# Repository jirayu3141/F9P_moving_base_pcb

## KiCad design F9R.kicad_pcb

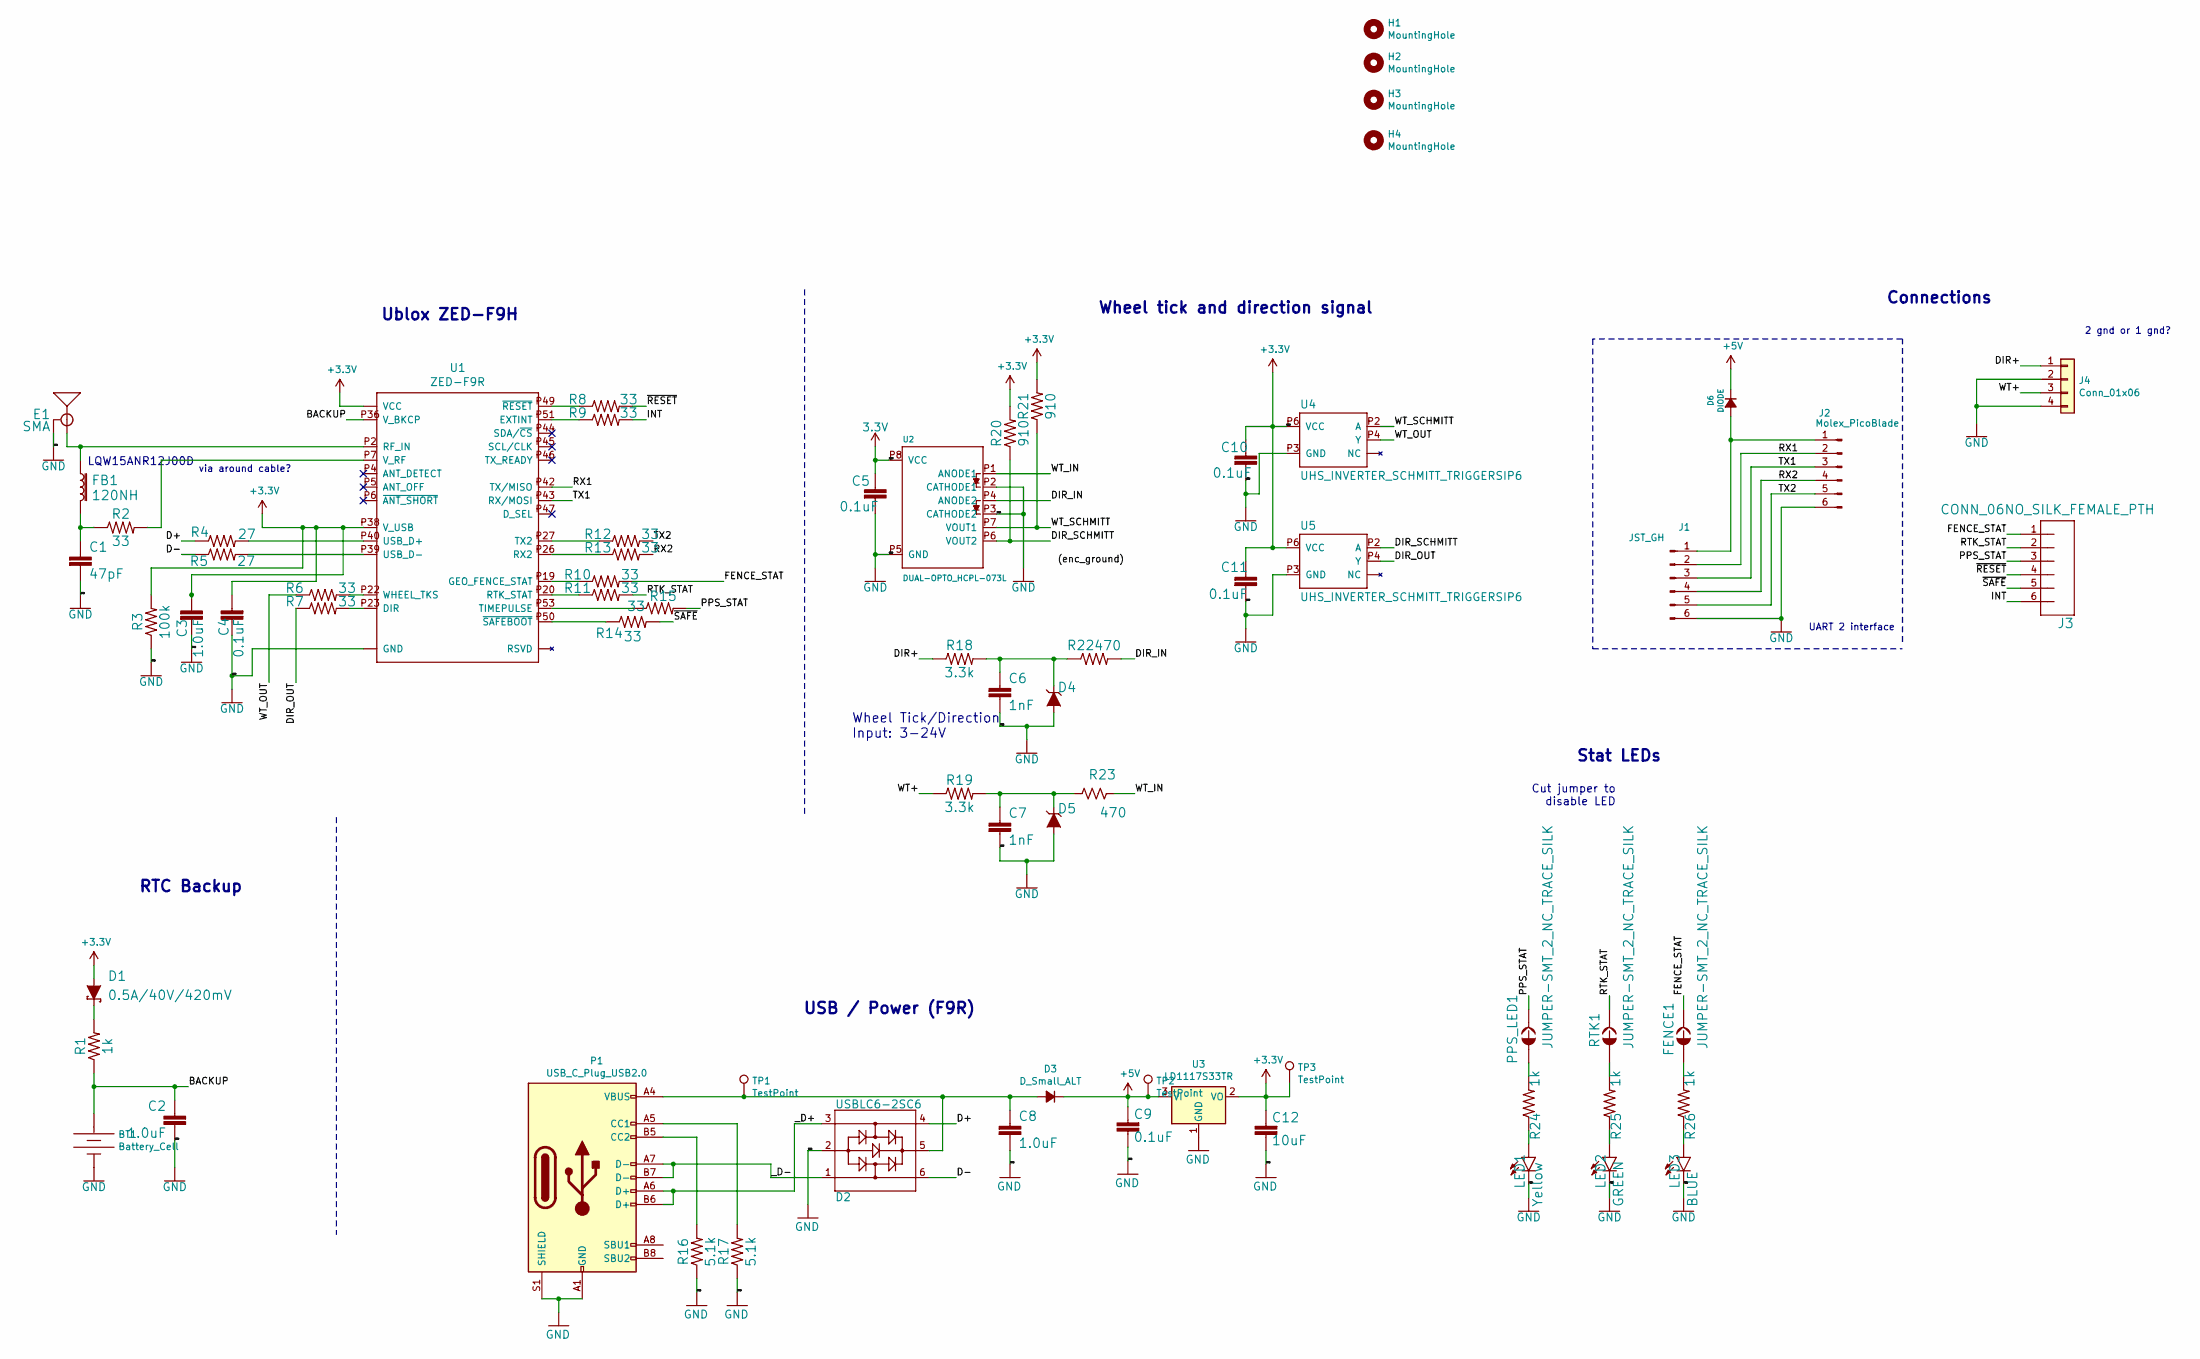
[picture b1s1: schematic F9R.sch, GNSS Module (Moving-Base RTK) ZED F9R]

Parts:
BT1: Battery_Cell; ML414H_IV01E; partno ML414H IV01E
C1: 47pF; 0402; partno 04023A470KAT2A
C2, C3, C8: 1.0uF; C_0603_1608Metric_Pad1.05x0.95mm_HandSolder; partno 0603YC105KAT2A
C4, C9: 0.1uF; C_0603_1608Metric_Pad1.05x0.95mm_HandSolder; partno 0603YC104KAT2A
C5: 0.1uF; 0402
C6, C7: 1nF; C_0603_1608Metric_Pad1.05x0.95mm_HandSolder
C10, C11: 0.1uF; C_0603_1608Metric_Pad1.05x0.95mm_HandSolder
C12: 10uF; C_0603_1608Metric_Pad1.05x0.95mm_HandSolder; partno 0603ZD106KAT2A
D1: 0.5A/40V/420mV; SOD-323; partno B0520WS-7-F
D2: USBLC6-2SC6; SOT-23-6; partno USBLC6-2SC6
D3: D_Small_ALT; SOD-80; partno LS4150GS08
D4, D5: 15V; SOT23-3
D6: DIODE; SOD-80; partno LS4150GS08
E1: SMA; SMA-EDGE; partno CON-SMA-EDGE-S
FB1: 120NH; 0402_MURATA; partno BLM15AG100SN1D
FENCE1: JUMPER-SMT_2_NC_TRACE_SILK; SMT-JUMPER_2_NC_TRACE_SILK
H1, H2, H3, H4: MountingHole; MountingHole_3.2mm_M3
J1: JST_GH; JST_GH_SM06B-GHS-TB_1x06-1MP_P1.25mm_Horizontal; partno SM06B-GHS-TB(LF)(SN)
J2: Molex_PicoBlade; Molex_PicoBlade_53261-0671_1x06-1MP_P1.25mm_Horizontal; partno 0532610671
J3: CONN_06NO_SILK_FEMALE_PTH; 1X06_NO_SILK
J4: Conn_01x06; Molex_CLIK-Mate_502443-0470_1x04-1MP_P2.00mm_Vertical
LED1: Yellow; LED-0603; partno LY Q396-P1Q2-36
LED2: GREEN; LED-0603; partno HSMG-C120
LED3: BLUE; LED-0603; partno 150060BS55040
P1: USB_C_Plug_USB2.0; USB_C_Receptacle_JAE_DX07S016JA1
PPS_LED1: JUMPER-SMT_2_NC_TRACE_SILK; SMT-JUMPER_2_NC_TRACE_SILK
R1: 1k; 0603; partno ERJ-3EKF1001V
R2, R6, R7, R8, R9, R10, R11, R12, R13, R14, R15: 33; R_0603_1608Metric_Pad1.05x0.95mm_HandSolder; partno ERJ-3EKF27R0V
R3: 100k; R_0603_1608Metric_Pad1.05x0.95mm_HandSolder; partno ERJ-3EKF1003V
R4, R5: 27; R_0603_1608Metric_Pad1.05x0.95mm_HandSolder; partno ERJ-3EKF27R0V
R16, R17: 5.1k; R_0603_1608Metric_Pad1.05x0.95mm_HandSolder; partno ERJ-3EKF5101V
R18, R19: 3.3k; R_0603_1608Metric_Pad1.05x0.95mm_HandSolder
R20, R21: 910; R_0603_1608Metric_Pad1.05x0.95mm_HandSolder
R22, R23: 470; R_0603_1608Metric_Pad1.05x0.95mm_HandSolder
R24, R25, R26: 1k; R_0603_1608Metric_Pad1.05x0.95mm_HandSolder; partno ERJ-3EKF1001V
RTK1: JUMPER-SMT_2_NC_TRACE_SILK; SMT-JUMPER_2_NC_TRACE_SILK
TP1, TP2, TP3: TestPoint; TestPoint_Pad_D1.0mm
U1: ZED-F9R; UBLOX_ZED_F9R
U2: DUAL-OPTO_HCPL-073L; SOP_8-PIN
U3: LD1117S33TR; SOT-223; partno LD1117S33TR
U4, U5: UHS_INVERTER_SCHMITT_TRIGGERSIP6; SIP6

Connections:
+3V3: C3.1, C4.2, C5.1, C10.1, C11.1, C12.2, D1.A, R3.2, R20.2, R21.2, TP3.1, U1.P33 (VCC), U1.P34 (VCC), U1.P38 (V_USB), U2.P8 (VCC), U3.2 (VO), U4.P6 (VCC), U5.P6 (VCC); also elsewhere on the board
+5V: C9.2, D3.1 (K), D6.1 (K), TP2.1, U3.3 (VI)
/BACKUP: BT1.+, C2.1, R1.1, U1.P36 (V_BKCP)
/D+: D2.4, R4.1
/D-: D2.6, R5.1
/DIR+: J4.1, R18.1
/DIR_IN: R22.2, U2.P4 (ANODE2)
/DIR_OUT: R7.1, U5.P4 (Y)
/DIR_SCHMITT: R20.1, U2.P6 (VOUT2), U5.P2 (A)
/FENCE_STAT: FENCE1.2, J3.1, R10.2
/INT: J3.6, R9.2
/PPS_STAT: J3.3, PPS_LED1.2, R15.2
/RTK_STAT: J3.2, R11.2, RTK1.2
/RX1: J1.2, J2.2, U1.P42 (TX/MISO)
/RX2: J1.4, J2.4, R13.2
/TX1: J1.3, J2.3, U1.P43 (RX/MOSI)
/TX2: J1.5, J2.5, R12.2
/WT+: J4.3, R19.1
/WT_IN: R23.1, U2.P1 (ANODE1)
/WT_OUT: R6.1, U4.P4 (Y)
/WT_SCHMITT: R21.1, U2.P7 (VOUT1), U4.P2 (A)
/_D+: D2.3, P1.A6 (D+), P1.B6 (D+)
/_D-: D2.1, P1.A7 (D-), P1.B7 (D-)
/~RESET: J3.4, R8.2
/~SAFE: J3.5, R14.2
GND: BT1.-, C1.2, C2.2, C3.2, C4.1, C5.2, C6.2, C7.2, C8.2, C9.1, C10.2, C11.2, C12.1, D2.2, D4.1 (A), D5.1 (A), E1.GND@0 (GND), E1.GND@1 (GND), E1.GND@2 (GND), E1.GND@3 (GND), J1.6, J2.6, J4.2, J4.4, LED1.C, LED2.C, LED3.C, P1.A1 (GND), P1.A12 (GND), P1.B1 (GND), P1.B12 (GND), P1.S1 (SHIELD), R3.1, R16.1, R17.1, U1.G1 (GND), U1.G2 (GND), U1.G3 (GND), U1.G4 (GND), U1.G5 (GND), U1.G6 (GND), U1.G7 (GND), U1.G8 (GND), U1.G9 (GND), U1.G10 (GND), U1.G11 (GND), U1.G12 (GND), U1.G13 (GND), U1.G14 (GND), U1.G15 (GND), U1.G16 (GND), U1.G17 (GND), U1.G18 (GND), U1.G19 (GND), U1.G20 (GND), U1.G21 (GND), U1.G22 (GND), U1.G23 (GND), U1.G24 (GND), U1.G25 (GND), U1.G26 (GND), U1.G27 (GND), U1.G28 (GND), U1.G29 (GND), U1.G30 (GND), U1.G31 (GND), U1.G32 (GND), U1.G33 (GND), U1.G34 (GND), U1.G35 (GND), U1.G36 (GND), U1.G37 (GND), U1.G38 (GND), U1.G39 (GND), U1.G40 (GND), U1.G41 (GND), U1.G42 (GND), U1.G43 (GND), U1.G44 (GND), U1.G45 (GND), U1.G46 (GND), U1.G47 (GND), U1.G48 (GND), U1.P1 (GND), U1.P3 (GND), U1.P12 (GND), U1.P14 (GND), U1.P32 (GND), U1.P37 (GND), U1.P41 (GND), U1.P48 (GND), U2.P2 (CATHODE1), U2.P3 (CATHODE2), U2.P5 (GND), U3.1 (GND), U4.P3 (GND), U5.P3 (GND); also elsewhere on the board
unnamed: C1.1, FB1.P2 (2), R2.1
unnamed: C6.1, D4.3 (C), R18.2, R22.1
unnamed: C7.1, D5.3 (C), R19.2, R23.2
unnamed: C8.1, D2.5, D3.2 (A), P1.A4 (VBUS), P1.A9 (VBUS), P1.B4 (VBUS), P1.B9 (VBUS), TP1.1
unnamed: D1.C, R1.2
unnamed: D6.2 (A), J1.1, J2.1
unnamed: E1.SIG (SIGNAL), FB1.P1 (1), U1.P2 (RF_IN)
unnamed: FENCE1.1, R26.2
unnamed: LED1.A, R24.1
unnamed: LED2.A, R25.1
unnamed: LED3.A, R26.1
unnamed: P1.A5 (CC1), R17.2
unnamed: P1.B5 (CC2), R16.2
unnamed: PPS_LED1.1, R24.2
unnamed: R2.2, U1.P7 (V_RF)
unnamed: R4.2, U1.P40 (USB_D+)
unnamed: R5.2, U1.P39 (USB_D-)
unnamed: R6.2, U1.P22 (WHEEL_TKS)
unnamed: R7.2, U1.P23 (DIR)
unnamed: R8.1, U1.P49 (~RESET~)
unnamed: R9.1, U1.P51 (EXTINT)
unnamed: R10.1, U1.P19 (GEO_FENCE_STAT)
unnamed: R11.1, U1.P20 (RTK_STAT)
unnamed: R12.1, U1.P27 (TX2)
unnamed: R13.1, U1.P26 (RX2)
unnamed: R14.1, U1.P50 (~SAFEBOOT~)
unnamed: R15.1, U1.P53 (TIMEPULSE)
unnamed: R25.2, RTK1.1

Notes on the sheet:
RTC Backup
USB / Power (F9R)
Ublox ZED-F9H
Cut jumper to disable LED
LQW15ANR12J00D
Stat LEDs
via around cable?
UART 2 interface
Wheel Tick/Direction Input: 3-24V
Wheel tick and direction signal
2 gnd or 1 gnd?
Connections

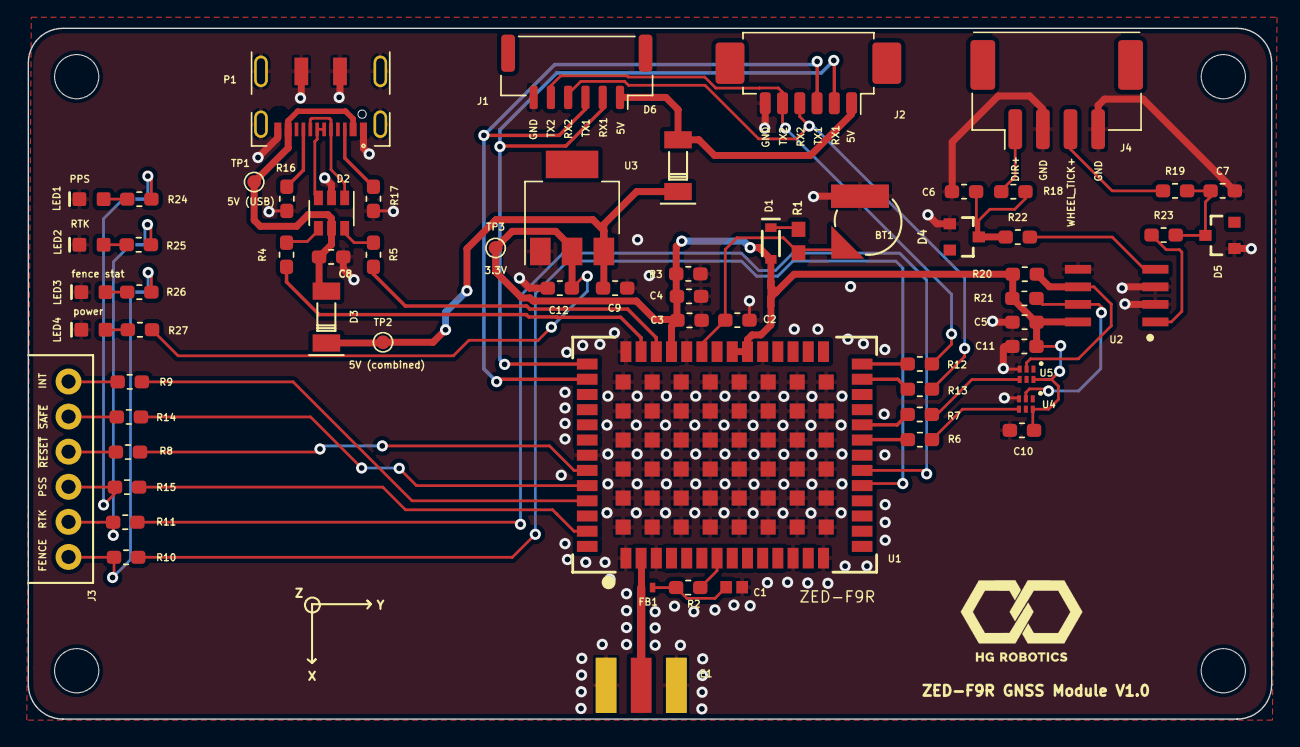
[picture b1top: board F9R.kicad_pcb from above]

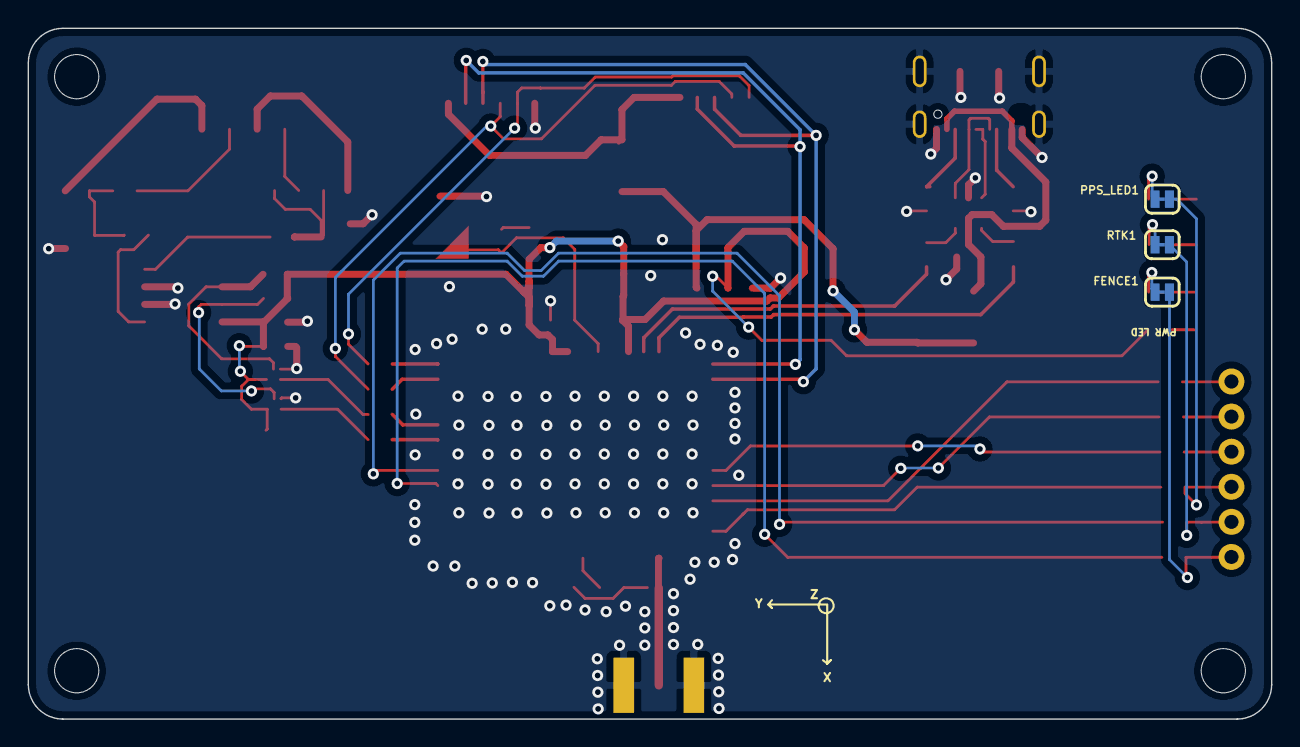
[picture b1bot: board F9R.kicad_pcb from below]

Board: 4 copper layers, 90.0 x 50.0 mm, 72 parts (3 on the bottom side), 55 nets.

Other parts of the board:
LED4: RED; LED-0603
R27: 1k; R_0603_1608Metric_Pad1.05x0.95mm_HandSolder

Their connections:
+3V3: R27.2; also elsewhere on the board
GND: LED4.C; also elsewhere on the board
unnamed: LED4.A, R27.1

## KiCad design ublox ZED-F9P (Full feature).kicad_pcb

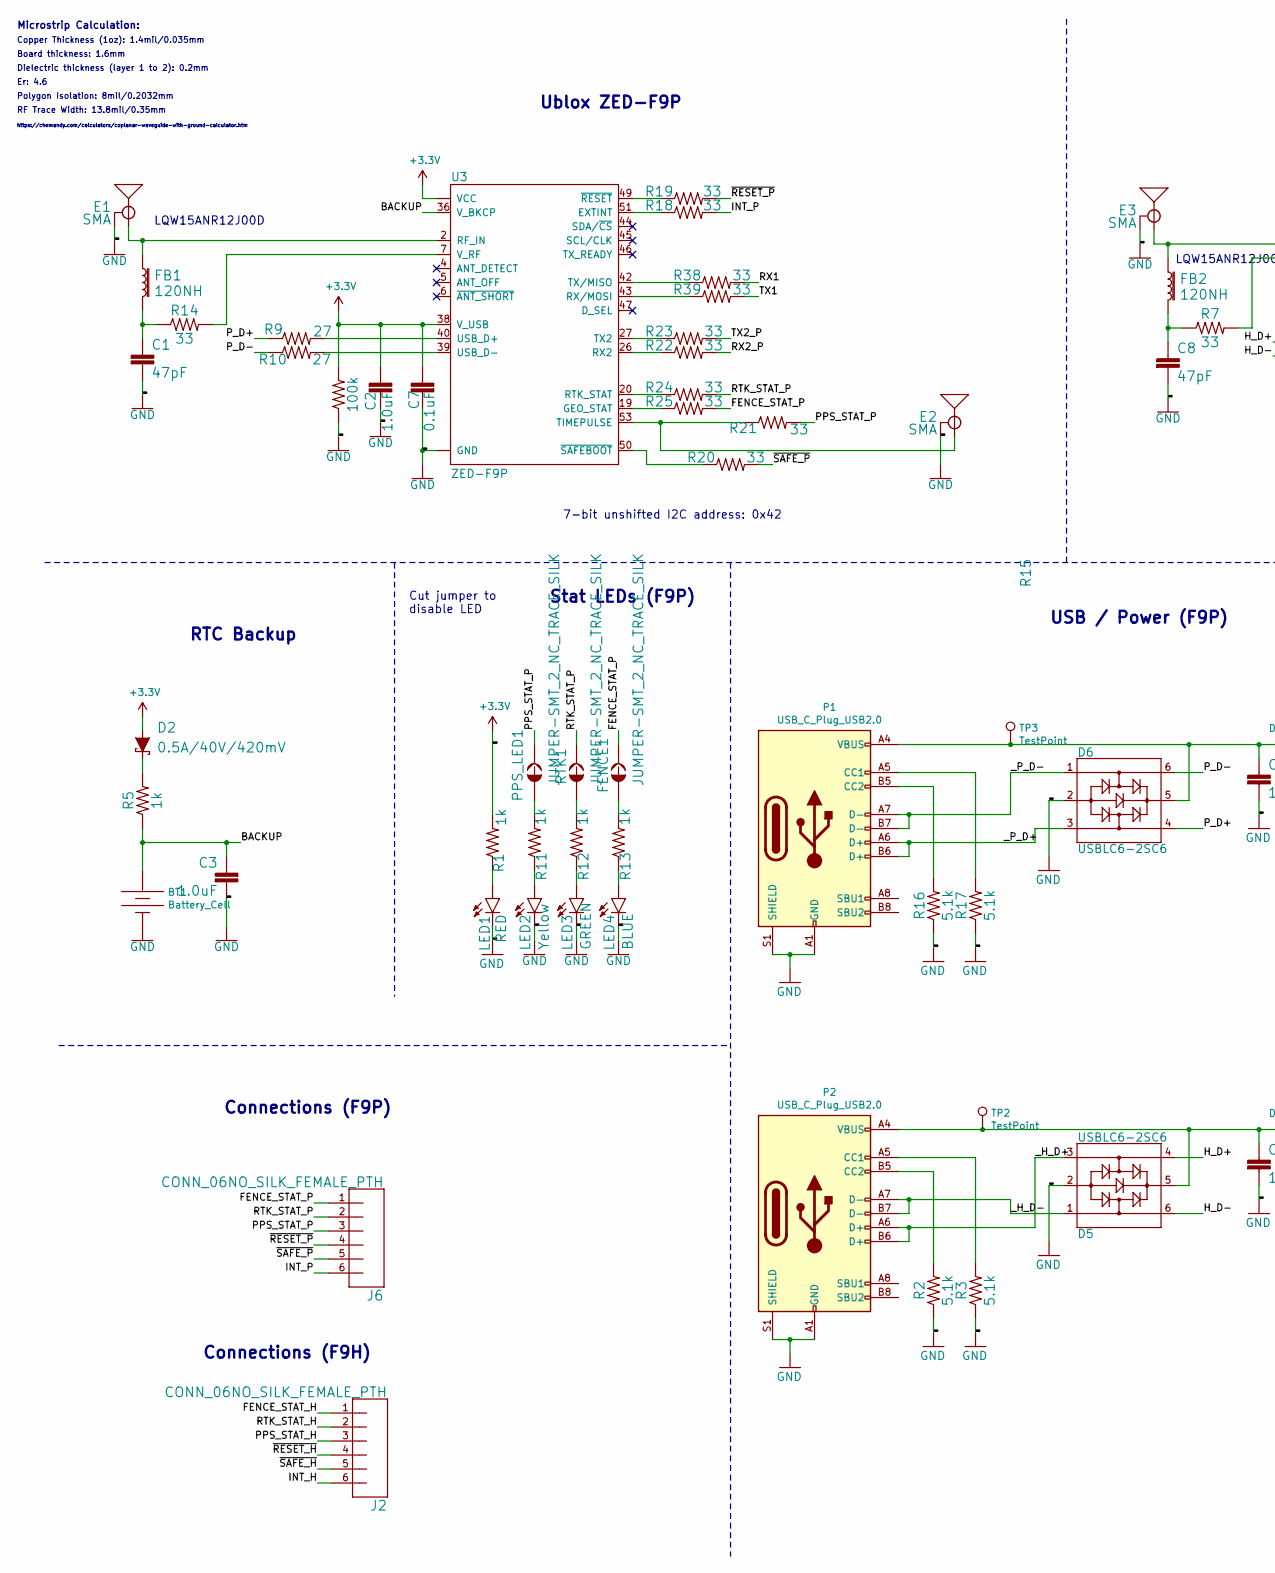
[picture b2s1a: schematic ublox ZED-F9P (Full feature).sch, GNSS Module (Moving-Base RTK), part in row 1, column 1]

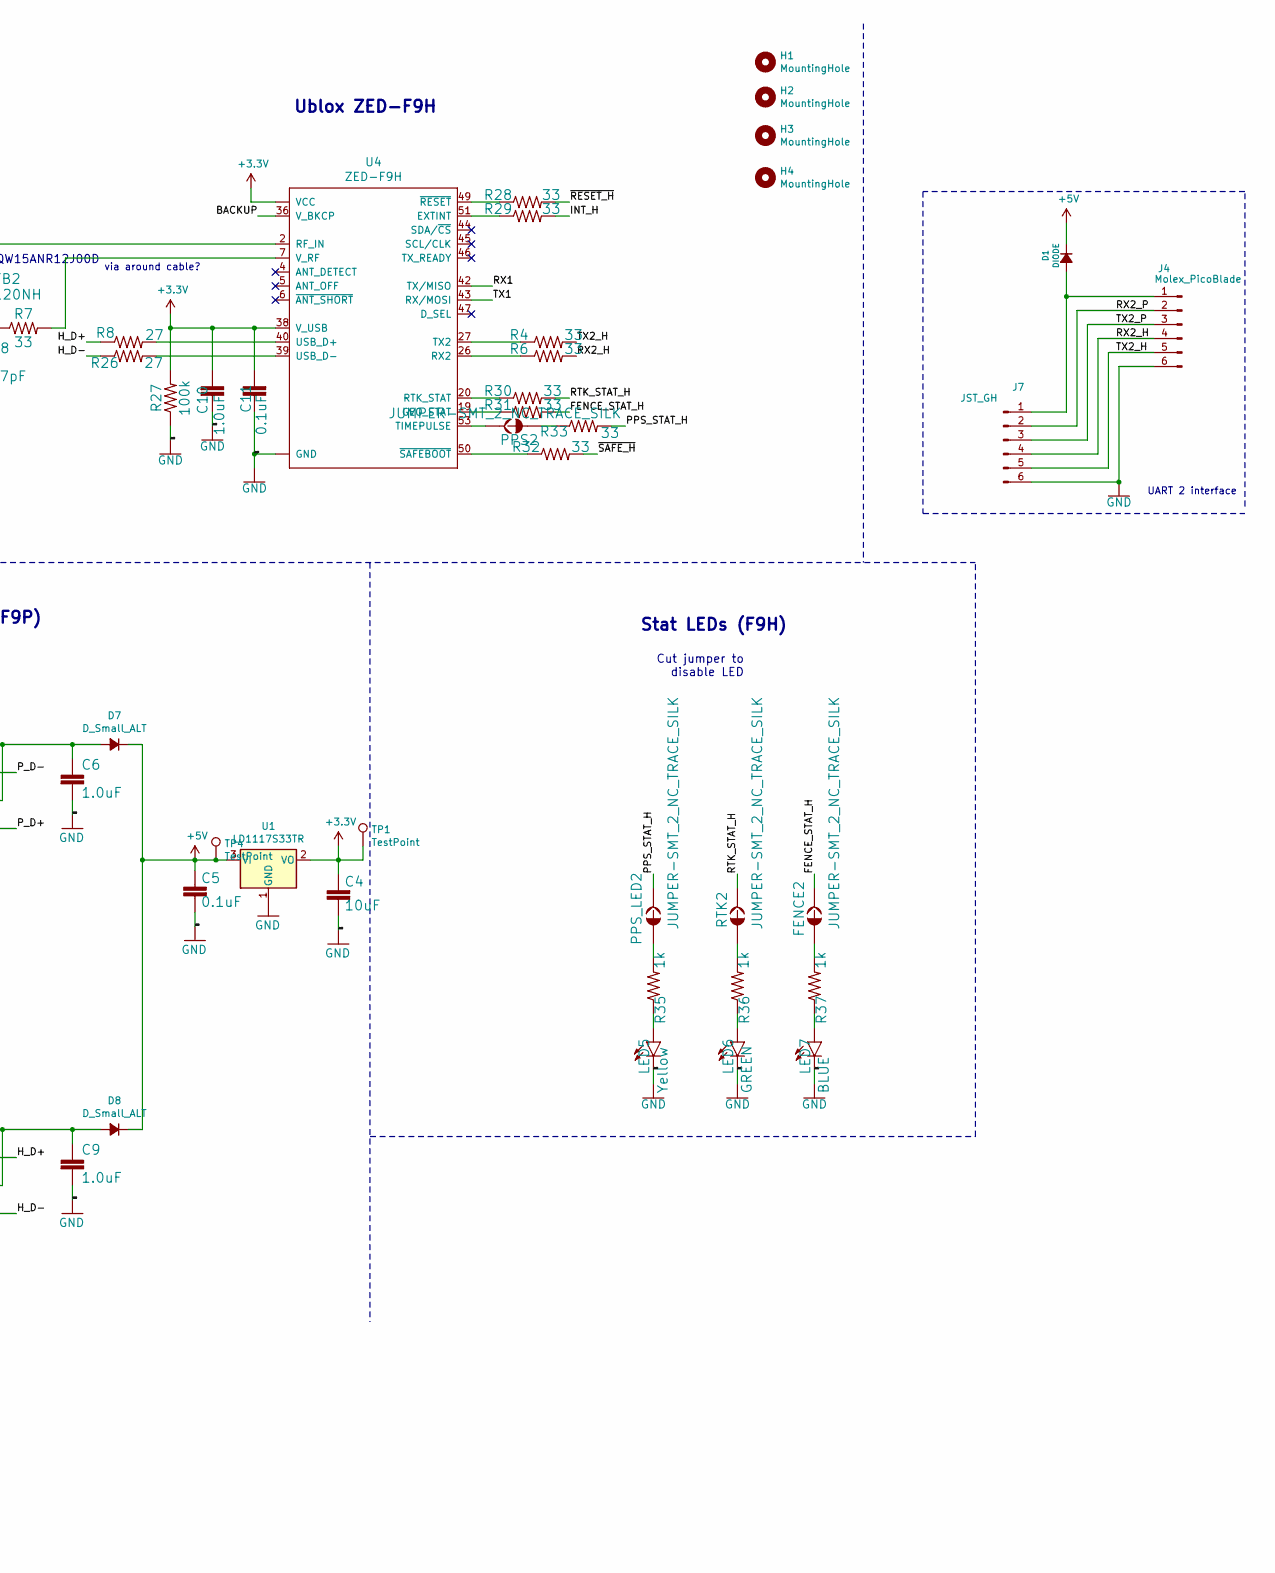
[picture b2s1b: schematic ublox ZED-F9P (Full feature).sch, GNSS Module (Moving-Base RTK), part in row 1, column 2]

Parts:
BT1: Battery_Cell; ML414H_IV01E; partno ML414H IV01E
C1, C8: 47pF; 0402; partno 04023A470KAT2A
C2, C3, C6, C9, C10: 1.0uF; C_0603_1608Metric_Pad1.05x0.95mm_HandSolder; partno 0603YC105KAT2A
C4: 10uF; C_0603_1608Metric_Pad1.05x0.95mm_HandSolder; partno 0603ZD106KAT2A
C5, C7, C11: 0.1uF; C_0603_1608Metric_Pad1.05x0.95mm_HandSolder; partno 0603YC104KAT2A
D1: DIODE; SOD-80; partno LS4150GS08
D2: 0.5A/40V/420mV; SOD-323; partno B0520WS-7-F
D5, D6: USBLC6-2SC6; SOT-23-6; partno USBLC6-2SC6
D7, D8: D_Small_ALT; SOD-80; partno LS4150GS08
E1, E2, E3: SMA; SMA-EDGE; partno CON-SMA-EDGE-S
FB1, FB2: 120NH; 0402_MURATA; partno BLM15AG100SN1D
FENCE1, FENCE2: JUMPER-SMT_2_NC_TRACE_SILK; SMT-JUMPER_2_NC_TRACE_SILK
H1, H2, H3, H4: MountingHole; MountingHole_3.2mm_M3
J2, J6: CONN_06NO_SILK_FEMALE_PTH; 1X06_NO_SILK
J4: Molex_PicoBlade; Molex_PicoBlade_53261-0671_1x06-1MP_P1.25mm_Horizontal; partno 0532610671
J7: JST_GH; JST_GH_SM06B-GHS-TB_1x06-1MP_P1.25mm_Horizontal; partno SM06B-GHS-TB(LF)(SN)
LED1: RED; LED-0603; partno HSMH-C191
LED2, LED5: Yellow; LED-0603; partno LY Q396-P1Q2-36
LED3, LED6: GREEN; LED-0603; partno HSMG-C120
LED4, LED7: BLUE; LED-0603; partno 150060BS55040
P1, P2: USB_C_Plug_USB2.0; USB_C_Receptacle_JAE_DX07S016JA1
PPS2: JUMPER-SMT_2_NC_TRACE_SILK; SMT-JUMPER_2_NC_TRACE_SILK
PPS_LED1, PPS_LED2: JUMPER-SMT_2_NC_TRACE_SILK; SMT-JUMPER_2_NC_TRACE_SILK
R1, R11, R12, R13, R35, R36, R37: 1k; R_0603_1608Metric_Pad1.05x0.95mm_HandSolder; partno ERJ-3EKF1001V
R2, R3, R16, R17: 5.1k; R_0603_1608Metric_Pad1.05x0.95mm_HandSolder; partno ERJ-3EKF5101V
R4, R6, R7, R14, R18, R19, R20, R21, R22, R23, R24, R25, R28, R29, R30, R31, R32, R33, R38, R39: 33; R_0603_1608Metric_Pad1.05x0.95mm_HandSolder; partno ERJ-3EKF27R0V
R5: 1k; 0603; partno ERJ-3EKF1001V
R8, R9, R10, R26: 27; R_0603_1608Metric_Pad1.05x0.95mm_HandSolder; partno ERJ-3EKF27R0V
R15, R27: 100k; R_0603_1608Metric_Pad1.05x0.95mm_HandSolder; partno ERJ-3EKF1003V
RTK1, RTK2: JUMPER-SMT_2_NC_TRACE_SILK; SMT-JUMPER_2_NC_TRACE_SILK
TP1, TP2, TP3, TP4: TestPoint; TestPoint_Pad_D1.0mm
U1: LD1117S33TR; SOT-223; partno LD1117S33TR
U3: ZED-F9P; partno ZED-F9P-01B
U4: ZED-F9H; ZED-F9P

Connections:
+3V3: C2.1, C4.2, C7.2, C10.1, C11.2, D2.A, R1.2, R15.2, R27.2, TP1.1, U1.2 (VO), U3.33 (VCC), U3.34 (VCC), U3.38 (V_USB), U4.33 (VCC), U4.34 (VCC), U4.38 (V_USB); also elsewhere on the board
+5V: C5.2, D1.1 (K), D7.1 (K), D8.1 (K), TP4.1, U1.3 (VI); also elsewhere on the board
/BACKUP: BT1.+, C3.1, R5.1, U3.36 (V_BKCP), U4.36 (V_BKCP)
/FENCE_STAT_H: FENCE2.2, J2.1, R31.2
/FENCE_STAT_P: FENCE1.2, J6.1, R25.2
/H_D+: D5.4, R8.1
/H_D-: D5.6, R26.1
/INT_H: J2.6, R29.2
/INT_P: J6.6, R18.2
/PPS_STAT_H: J2.3, PPS_LED2.2, R33.2
/PPS_STAT_P: J6.3, PPS_LED1.2, R21.2
/P_D+: D6.4, R9.1
/P_D-: D6.6, R10.1
/RTK_STAT_H: J2.2, R30.2, RTK2.2
/RTK_STAT_P: J6.2, R24.2, RTK1.2
/RX1: R38.2, U4.42 (TX/MISO)
/RX2_H: J4.4, J7.4, R6.2
/RX2_P: J4.2, J7.2, R22.2
/TX1: R39.2, U4.43 (RX/MOSI)
/TX2_H: J4.5, J7.5, R4.2
/TX2_P: J4.3, J7.3, R23.2
/_H_D+: D5.3, P2.A6 (D+), P2.B6 (D+)
/_H_D-: D5.1, P2.A7 (D-), P2.B7 (D-)
/_P_D+: D6.3, P1.A6 (D+), P1.B6 (D+)
/_P_D-: D6.1, P1.A7 (D-), P1.B7 (D-)
/~RESET_H: J2.4, R28.2
/~RESET_P: J6.4, R19.2
/~SAFE_H: J2.5, R32.2
/~SAFE_P: J6.5, R20.2
GND: BT1.-, C1.2, C2.2, C3.2, C4.1, C5.1, C6.2, C7.1, C8.2, C9.2, C10.2, C11.1, D5.2, D6.2, E1.GND@0 (GND), E1.GND@1 (GND), E1.GND@2 (GND), E1.GND@3 (GND), E2.GND@0 (GND), E2.GND@1 (GND), E2.GND@2 (GND), E2.GND@3 (GND), E3.GND@0 (GND), E3.GND@1 (GND), E3.GND@2 (GND), E3.GND@3 (GND), J4.6, J7.6, LED1.C, LED2.C, LED3.C, LED4.C, LED5.C, LED6.C, LED7.C, P1.A1 (GND), P1.A12 (GND), P1.B1 (GND), P1.B12 (GND), P1.S1 (SHIELD), P2.A1 (GND), P2.A12 (GND), P2.B1 (GND), P2.B12 (GND), P2.S1 (SHIELD), R2.1, R3.1, R15.1, R16.1, R17.1, R27.1, U1.1 (GND), U3.1 (GND), U3.3 (GND), U3.12 (GND), U3.14 (GND), U3.32 (GND), U3.37 (GND), U3.41 (GND), U3.48 (GND), U3.55 (GND), U3.56 (GND), U3.57 (GND), U3.58 (GND), U3.59 (GND), U3.60 (GND), U3.61 (GND), U3.62 (GND), U3.63 (GND), U3.64 (GND), U3.65 (GND), U3.66 (GND), U3.67 (GND), U3.68 (GND), U3.69 (GND), U3.70 (GND), U3.71 (GND), U3.72 (GND), U3.73 (GND), U3.74 (GND), U3.75 (GND), U3.76 (GND), U3.77 (GND), U3.78 (GND), U3.79 (GND), U3.80 (GND), U3.81 (GND), U3.82 (GND), U3.83 (GND), U3.84 (GND), U3.85 (GND), U3.86 (GND), U3.87 (GND), U3.88 (GND), U3.89 (GND), U3.90 (GND), U3.91 (GND), U3.92 (GND), U3.93 (GND), U3.94 (GND), U3.95 (GND), U3.96 (GND), U3.97 (GND), U3.98 (GND), U3.99 (GND), U3.100 (GND), U3.101 (GND), U3.102 (GND), U4.1 (GND), U4.3 (GND), U4.12 (GND), U4.14 (GND), U4.32 (GND), U4.37 (GND), U4.41 (GND), U4.48 (GND), U4.55 (GND), U4.56 (GND), U4.57 (GND), U4.58 (GND), U4.59 (GND), U4.60 (GND), U4.61 (GND), U4.62 (GND), U4.63 (GND), U4.64 (GND), U4.65 (GND), U4.66 (GND), U4.67 (GND), U4.68 (GND), U4.69 (GND), U4.70 (GND), U4.71 (GND), U4.72 (GND), U4.73 (GND), U4.74 (GND), U4.75 (GND), U4.76 (GND), U4.77 (GND), U4.78 (GND), U4.79 (GND), U4.80 (GND), U4.81 (GND), U4.82 (GND), U4.83 (GND), U4.84 (GND), U4.85 (GND), U4.86 (GND), U4.87 (GND), U4.88 (GND), U4.89 (GND), U4.90 (GND), U4.91 (GND), U4.92 (GND), U4.93 (GND), U4.94 (GND), U4.95 (GND), U4.96 (GND), U4.97 (GND), U4.98 (GND), U4.99 (GND), U4.100 (GND), U4.101 (GND), U4.102 (GND)
unnamed: C1.1, FB1.P2 (2), R14.1
unnamed 31: C6.1, D6.5, D7.2 (A), P1.A4 (VBUS), P1.A9 (VBUS), P1.B4 (VBUS), P1.B9 (VBUS), TP3.1; also elsewhere on the board
unnamed: C8.1, FB2.P2 (2), R7.1
unnamed 33: C9.1, D5.5, D8.2 (A), P2.A4 (VBUS), P2.A9 (VBUS), P2.B4 (VBUS), P2.B9 (VBUS), TP2.1; also elsewhere on the board
unnamed: D1.2 (A), J4.1, J7.1
unnamed: D2.C, R5.2
unnamed: E1.SIG (SIGNAL), FB1.P1 (1), U3.2 (RF_IN)
unnamed: E2.SIG (SIGNAL), R21.1, U3.53 (TIMEPULSE)
unnamed: E3.SIG (SIGNAL), FB2.P1 (1), U4.2 (RF_IN)
unnamed: FENCE1.1, R13.2
unnamed: FENCE2.1, R37.2
unnamed: LED1.A, R1.1
unnamed: LED2.A, R11.1
unnamed: LED3.A, R12.1
unnamed: LED4.A, R13.1
unnamed: LED5.A, R35.1
unnamed: LED6.A, R36.1
unnamed: LED7.A, R37.1
unnamed: P1.A5 (CC1), R17.2
unnamed: P1.B5 (CC2), R16.2
unnamed: P2.A5 (CC1), R3.2
unnamed: P2.B5 (CC2), R2.2
unnamed: PPS2.1, R33.1
unnamed: PPS2.2, U4.53 (TIMEPULSE)
unnamed: PPS_LED1.1, R11.2
unnamed: PPS_LED2.1, R35.2
unnamed: R4.1, U4.27 (TX2)
unnamed: R6.1, U4.26 (RX2)
unnamed: R7.2, U4.7 (V_RF)
unnamed: R8.2, U4.40 (USB_D+)
unnamed: R9.2, U3.40 (USB_D+)
unnamed: R10.2, U3.39 (USB_D-)
unnamed: R12.2, RTK1.1
unnamed: R14.2, U3.7 (V_RF)
unnamed: R18.1, U3.51 (EXTINT)
unnamed: R19.1, U3.49 (~RESET~)
unnamed: R20.1, U3.50 (~SAFEBOOT~)
unnamed: R22.1, U3.26 (RX2)
unnamed: R23.1, U3.27 (TX2)
unnamed: R24.1, U3.20 (RTK_STAT)
unnamed: R25.1, U3.19 (GEO_STAT)
unnamed: R26.2, U4.39 (USB_D-)
unnamed: R28.1, U4.49 (~RESET~)
unnamed: R29.1, U4.51 (EXTINT)
unnamed: R30.1, U4.20 (RTK_STAT)
unnamed: R31.1, U4.19 (GEO_STAT)
unnamed: R32.1, U4.50 (~SAFEBOOT~)
unnamed: R36.2, RTK2.1
unnamed: R38.1, U3.42 (TX/MISO)
unnamed: R39.1, U3.43 (RX/MOSI)

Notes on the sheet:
7-bit unshifted I2C address: 0x42
Ublox ZED-F9P
RTC Backup
Cut jumper to disable LED
LQW15ANR12J00D
Board thickness: 1.6mm
Er: 4.6
Copper Thickness (1oz): 1.4mil/0.035mm
RF Trace Width: 13.8mil/0.35mm
Polygon Isolation: 8mil/0.2032mm
Dielectric thickness (layer 1 to 2): 0.2mm
https://chemandy.com/calculators/coplanar-waveguide-with-ground-calculator.htm
Microstrip Calculation:
Connections (F9P)
USB / Power (F9P)
Ublox ZED-F9H
Stat LEDs (F9P)
Stat LEDs (F9H)
Connections (F9H)
via around cable?
UART 2 interface

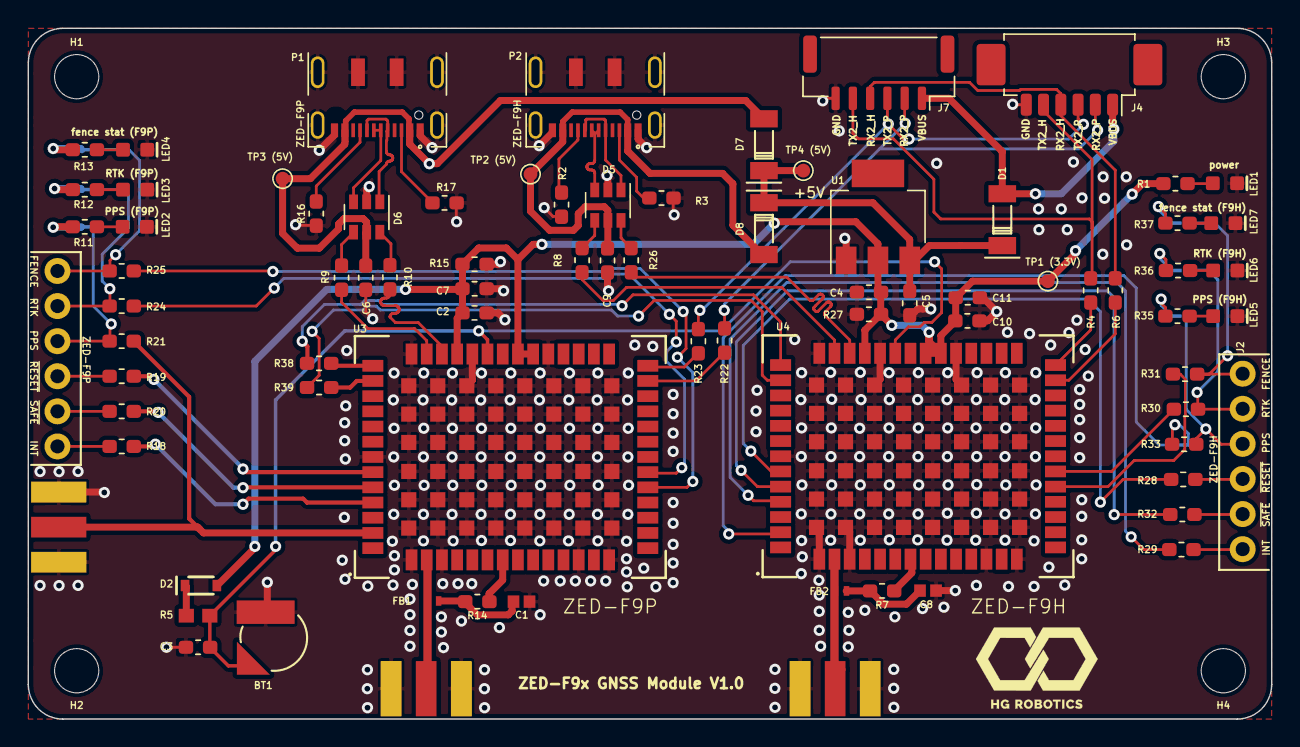
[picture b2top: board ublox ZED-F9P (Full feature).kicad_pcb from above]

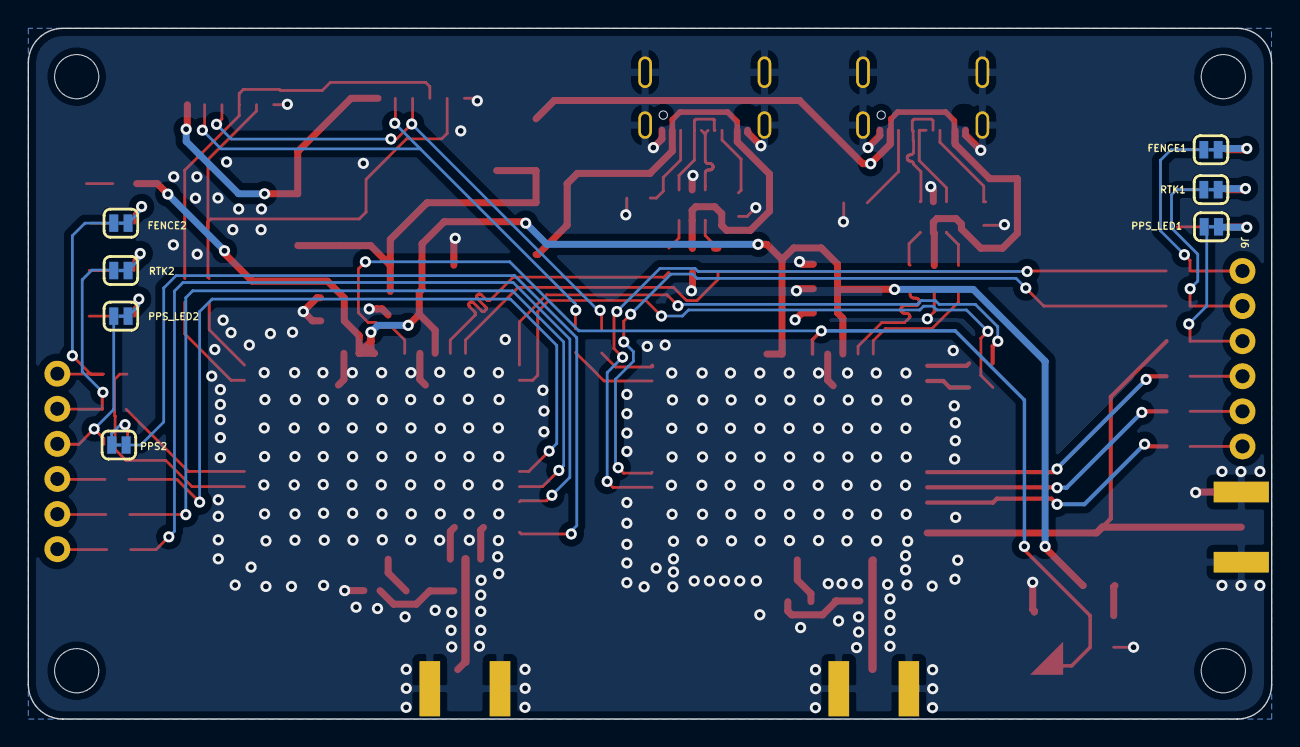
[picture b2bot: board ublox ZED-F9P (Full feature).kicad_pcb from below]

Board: 4 copper layers, 90.0 x 50.0 mm, 92 parts (8 on the bottom side), 80 nets.

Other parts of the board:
TP1 (3.3V), TP2 (5V), TP3 (5V), TP4 (5V): TestPoint; TestPoint_Pad_D1.0mm

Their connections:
+3V3: TP1 (3.3V).1; also elsewhere on the board
+5V: TP4 (5V).1; also elsewhere on the board
unnamed 31: TP3 (5V).1; also elsewhere on the board
unnamed 33: TP2 (5V).1; also elsewhere on the board

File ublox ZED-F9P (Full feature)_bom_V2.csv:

Component,Description,Part,References,Value,Footprint,Quantity Per PCB,Datasheet,partno,Approval,Detailed Description,Series
1,,ML414H_IV01E_BATTERY-Qwiic_GPS-RTK-SMA_-_ublox_ZED-F9P-eagle-import,BT1,Battery_Cell,ML414H_IV01E,1,,ML414H IV01E,,,
2,,47PF-0402-25V-5%-X7R-Qwiic_GPS-RTK-SMA_-_ublox_ZED-F9P-eagle-import,C1 C8,47pF,0402,2,,04023A470KAT2A,,,
3,,0.1UF-0603-25V-5%-Qwiic_GPS-RTK-SMA_-_ublox_ZED-F9P-eagle-import,C5 C7 C11,0.1uF,C_0603_1608Metric_Pad1.05x0.95mm_HandSolder,3,,0603YC104KAT2A,,,
4,,1.0UF-0603-16V-10%-X7R-Qwiic_GPS-RTK-SMA_-_ublox_ZED-F9P-eagle-import,C2 C3 C6 C9 C10,1.0uF,C_0603_1608Metric_Pad1.05x0.95mm_HandSolder,5,,0603YC105KAT2A,,,
5,,0.1UF-0603-25V-5%-Qwiic_GPS-RTK-SMA_-_ublox_ZED-F9P-eagle-import,C4,10uF,C_0603_1608Metric_Pad1.05x0.95mm_HandSolder,1,,0603ZD106KAT2A,,,
6,,DIODE-SCHOTTKY-PMEG4005EJ-Qwiic_GPS-RTK-SMA_-_ublox_ZED-F9P-eagle-import,D2,0.5A/40V/420mV,SOD-323,1,,B0520WS-7-F,,,
7,"Diode, small symbol, filled shape",D_Small_ALT,D12,DIODE,SOD-80,1,https://www.digikey.co.th/product-detail/en/vishay-semicondu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,LS4150GS08,Approved,,
8,"Diode, small symbol, filled shape",D_Small_ALT,D7 D8,D_Small_ALT,SOD-80,2,https://www.digikey.co.th/product-detail/en/vishay-semicondu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,LS4150GS08,,,
9,,PRTR5V0U2F-Qwiic_GPS-RTK-SMA_-_ublox_ZED-F9P-eagle-import,D5 D6,USBLC6-2SC6,SOT-23-6,2,CON-SMA-EDGE-S,USBLC6-2SC6,,,
10,,ANTENNA-GROUNDEDEDGE_SMA-Qwiic_GPS-RTK-SMA_-_ublox_ZED-F9P-eagle-import,E1 E2 E3,SMA,SMA-EDGE,3,https://www.digikey.com/product-detail/en/rf-solutions/CON-S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,CON-SMA-EDGE-S,,,
11,,FERRITE_BEAD_GNSS-Qwiic_GPS-RTK-SMA_-_ublox_ZED-F9P-eagle-import,FB1 FB2,120NH,0402_MURATA,2,https://www.digikey.com/product-detail/en/murata-electronics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,BLM15AG100SN1D,,180 Ohms @ 100MHz 1 Ferrite Bead 0603 (1608 Metric) 2A 50mOhm,
12,,JUMPER-SMT_2_NC_TRACE_SILK-Qwiic_GPS-RTK-SMA_-_ublox_ZED-F9P-eagle-import,FENCE1 FENCE2 PPS2 PPS_LED1 PPS_LED2 RTK1 RTK2,JUMPER-SMT_2_NC_TRACE_SILK,SMT-JUMPER_2_NC_TRACE_SILK,7,,-,,,
13,,CONN_06NO_SILK_FEMALE_PTH-Qwiic_GPS-RTK-SMA_-_ublox_ZED-F9P-eagle-import,J2 J6,CONN_06NO_SILK_FEMALE_PTH,1X06_NO_SILK,2,,,,,
14,"Generic connector, single row, 01x06, script generated (kicad-library-utils/schlib/autogen/connector/)",Conn_01x06_Male,J7,JST_GH,JST_GH_SM06B-GHS-TB_1x06-1MP_P1.25mm_Horizontal,1,https://www.digikey.com/product-detail/en/jst-sales-america-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,SM06B-GHS-TB(LF)(SN),Approved,"Connector Header Surface Mount, Right Angle 6 position 0.049"" (1.25mm)",GH
15,"Generic connector, single row, 01x06, script generated (kicad-library-utils/schlib/autogen/connector/)",Conn_01x06_Male,J4,Molex_PicoBlade,Molex_PicoBlade_53261-0671_1x06-1MP_P1.25mm_Horizontal,1,https://www.digikey.com/product-detail/en/molex/0532610671/W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,0532610671,Approved,"Connector Header Surface Mount, Right Angle 6 position 0.049"" (1.25mm)",
16,,LED-BLUE0603-Qwiic_GPS-RTK-SMA_-_ublox_ZED-F9P-eagle-import,LED4 LED7,BLUE,LED-0603,2,https://www.digikey.com/product-detail/en/w%C3%BCrth-elektro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,150060BS55040,,Blue 470nm LED Indication - Discrete 3.2V 0603 (1608 Metric),
17,,LED-GREEN0603-Qwiic_GPS-RTK-SMA_-_ublox_ZED-F9P-eagle-import,LED3 LED6,GREEN,LED-0603,2,,HSMG-C120,,,
18,,LED-RED0603-Qwiic_GPS-RTK-SMA_-_ublox_ZED-F9P-eagle-import,LED1,RED,LED-0603,1,,HSMH-C191,,,
19,,LED-YELLOW0603-Qwiic_GPS-RTK-SMA_-_ublox_ZED-F9P-eagle-import,LED2 LED5,Yellow,LED-0603,2,https://www.digikey.com/product-detail/en/osram-opto-semicon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,LY Q396-P1Q2-36,,,
20,USB 2.0-only Type-C Receptacle connector,USB_C_Receptacle_USB2.0,P1 P2,USB_C_Plug_USB2.0,USB_C_Receptacle_JAE_DX07S016JA1,2,https://www.mouser.com/ProductDetail/JAE-Electronics/DX07S01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,,,,
21,,27OHM-0603-1_10W-1%-Qwiic_GPS-RTK-SMA_-_ublox_ZED-F9P-eagle-import,R8 R9 R10 R26,27,R_0603_1608Metric_Pad1.05x0.95mm_HandSolder,4,,ERJ-3EKF27R0V,,,
22,,33OHM-0603-1_10W-1%-Qwiic_GPS-RTK-SMA_-_ublox_ZED-F9P-eagle-import,R4 R6 R7 R14 R18 R19 R20 R21 R22 R23 R24 R25 R28 R29 R30 R31 R32 R33 R38 R39,33,R_0603_1608Metric_Pad1.05x0.95mm_HandSolder,20,,ERJ-3EKF27R0V,,,
23,,1KOHM-0603-1_10W-1%-Qwiic_GPS-RTK-SMA_-_ublox_ZED-F9P-eagle-import,R1 R5 R11 R12 R13 R35 R36 R37,1k,R_0603_1608Metric_Pad1.05x0.95mm_HandSolder,8,,ERJ-3EKF1001V,,,
24,,5.1KOHM5.1KOHM-0603-1_10W-1%-Qwiic_GPS-RTK-SMA_-_ublox_ZED-F9P-eagle-import,R2 R3 R16 R17,5.1k,R_0603_1608Metric_Pad1.05x0.95mm_HandSolder,4,,ERJ-3EKF5101V,,,
25,,100KOHM-0603-1_10W-1%-Qwiic_GPS-RTK-SMA_-_ublox_ZED-F9P-eagle-import,R15 R27,100k,R_0603_1608Metric_Pad1.05x0.95mm_HandSolder,2,,ERJ-3EKF1003V,,,
26,"800mA Low-Dropout Linear Regulator, 3.3V fixed output, TO-220/TO-252/TO-263/SOT-223",LM1117-3.3,U1,LD1117S33TR,SOT-223,1,http://www.ti.com/lit/ds/symlink/lm1117.pdf,LD1117S33TR,,,
27,,ZED-F9H-Qwiic_GPS-RTK-SMA_-_ublox_ZED-F9P-eagle-import,U4,ZED-F9H,ZED-F9P,1,,,,,
28,,ZED-F9P-Qwiic_GPS-RTK-SMA_-_ublox_ZED-F9P-eagle-import,U3,ZED-F9P,ZED-F9P,1,,ZED-F9P-01B,,,





Component Groups:,28
Component Count:,84
Fitted Components:,84
Number of PCBs:,1
Total components:,84
Schematic Version:,V2
Schematic Date:,2020-09-17
PCB Variant:,[u'default']
BoM Date:,"Thursday, 01 October 2020 at 04:44:36 pm"
Schematic Source:,ublox ZED-F9P (Full feature).sch
KiCad Version:,Eeschema (5.1.6-0-10_14)

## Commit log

2020-09-23 name changed
2020-09-23 Try pushing this repo
2020-09-23 Update partno
2020-09-23 part no updated
2020-09-24 removed unescessary resistors
2020-09-24 added extras
2020-09-24 removed SMA time paulse from F9H
2020-09-26 changed usb c
2020-09-29 changed usb c differential pair
2020-10-01 finished routing
2020-10-01 updated new consistent footprint and silkscreen
2020-10-01 updated silkscreen
2020-10-01 added logo;
2020-10-01 finished export
2020-10-02 finished v1.1
2020-10-02 genereated output
2020-10-02 deleted unused files
2020-10-06 routed f9r
2020-10-06 rearrange silkscreen H1-H4,P1-P2,J4,J7 remove bottom silkscreen PWR LED resize all footprint references to height0.5,width0.5,thichness0.1 mm Add silkscreen label for pins of J2,J4,J6, J7
2020-10-06 finished f9r
2020-10-06 added logo
2020-10-06 adjusted label
2020-10-06 added direction to the back
2020-10-06 edited silk screen
2020-10-06 edited silk screen to 0.5, 0.5, 0.1 size
2020-10-06 Add HGR logo
2020-10-06 Add gerber.zip
2020-10-07 redy for check
2020-10-07 added silkscreen to testpoint
2020-10-07 edited BOM
2020-10-07 update gerber files
